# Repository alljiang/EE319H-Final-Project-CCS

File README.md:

# EE319H-Final-Project-CCS
Smash Bros TM4C edition, written in Code Exploder Studio. Using custom drivers and framework.  
Submission for the final project (lab 10 game design competition) of EE319H.  

Features:  
  • 3 characters: Kirby, Game and Watch, and a newcomer: Dr. Jon Valvano  
  • 6 stages: Final Destination, Battlefield, Smashville, UT Main Mall (original), UT EER (original), UT Gregory Gym (original)  
  • 32K audio SD card streaming  
  • Master-Slave controller interface between TM4Cs   
&nbsp;&nbsp;&nbsp;&nbsp;&nbsp;&nbsp;‣ Master controller receives player inputs from both controllers and controls game logic and audio  
&nbsp;&nbsp;&nbsp;&nbsp;&nbsp;&nbsp;‣ Slave controller receives sprite data from Master controller and updates both LCD displays  
  • 1 megabyte flash memory used by slave controller for fast access to raw sprite data  
  • Custom drivers for flash memory and ILI9341 LCD display  
  • Custom PCB - schematic and 3D assembly included in files   
  • [Game Simulator](https://github.com/alljiang/EE319H-Final-Project-Simulation), which was used to develop the 8000+ lines of game logic  

Watch the demo here: https://www.youtube.com/watch?v=PevV5ol1qZk

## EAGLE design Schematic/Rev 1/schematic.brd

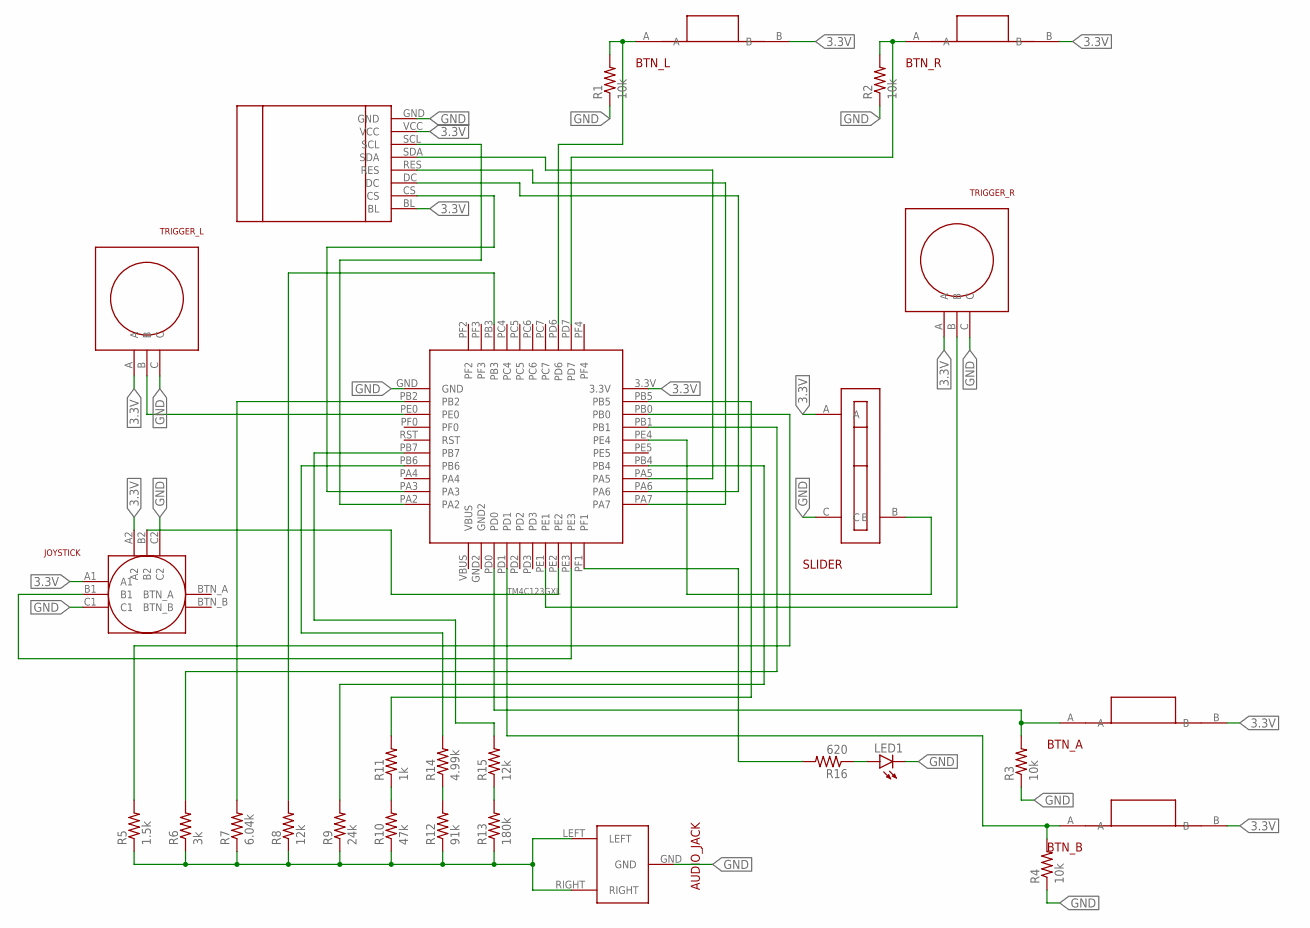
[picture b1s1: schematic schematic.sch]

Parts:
LED1: LEDCHIPLED_1206; CHIPLED_1206
R1, R2, R3, R4: 10k; R0805
R5: 1.5k; R0805
R6: 3k; R0805
R7: 6.04k; R0805
R8, R15: 12k; R0805
R9: 24k; R0805
R10: 47k; R0805
R11: 1k; R0805
R12: 91k; R0805
R13: 180k; R0805
R14: 4.99k; R0805
R16: 620; R0805
U$1: TM4C123GXL
U$2: JOYSTICK
U$3: BTN_L; RIGHT_ANGLE_BUTTON
U$4: BTN_R; RIGHT_ANGLE_BUTTON
U$5: TRIGGER_L
U$6: TRIGGER_R
U$7: SLIDER
U$8: BTN_A; BUTTON
U$9: BTN_B; BUTTON
U$10: AUDIO_JACK
U$11: LCD_SCREEN

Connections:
3.3V: U$1.3.3V, U$2.A1, U$2.A2, U$3.B, U$4.B, U$5.A, U$6.A, U$7.A, U$8.B, U$9.B, U$11.BL, U$11.VCC
GND: LED1.C, R1.1, R2.1, R3.1, R4.1, U$1.GND, U$2.C1, U$2.C2, U$5.C, U$6.C, U$7.C, U$10.GND, U$11.GND
unnamed: U$1.PE4, U$7.B
unnamed: U$1.PE0, U$5.B
unnamed: U$1.PE1, U$6.B
unnamed: U$1.PE2, U$2.B2
unnamed: R16.2, U$1.PF1
unnamed: R4.2, U$1.PD1, U$9.A
unnamed: R10.2, R11.1
unnamed: R2.2, U$1.PD7, U$4.A
unnamed: R1.2, U$1.PD6, U$3.A
unnamed: R12.2, R14.1
unnamed: U$1.PA2, U$11.SCL
unnamed: U$1.PA5, U$11.SDA
unnamed: U$1.PA7, U$11.RES
unnamed: U$1.PA6, U$11.DC
unnamed: U$1.PA3, U$11.CS
unnamed: R13.2, R15.1
unnamed: R5.1, R6.1, R7.1, R8.1, R9.1, R10.1, R12.1, R13.1, U$10.LEFT, U$10.RIGHT
unnamed: R5.2, U$1.PB0
unnamed: R6.2, U$1.PB1
unnamed: R7.2, U$1.PB2
unnamed: R8.2, U$1.PB3
unnamed: R9.2, U$1.PB4
unnamed: R11.2, U$1.PB5
unnamed: R14.2, U$1.PB6
unnamed: R15.2, U$1.PB7
unnamed: R3.2, U$1.PD0, U$8.A
unnamed: LED1.A, R16.1
unnamed: U$1.PE3, U$2.B1

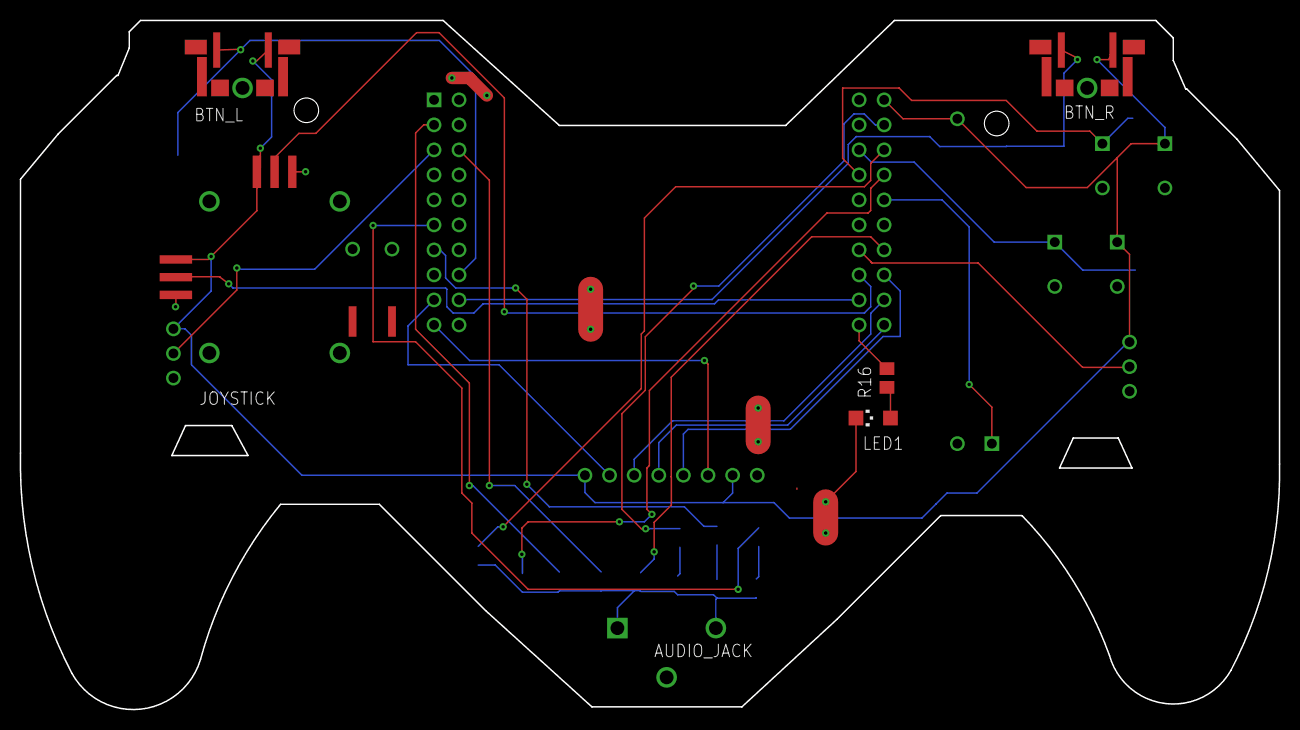
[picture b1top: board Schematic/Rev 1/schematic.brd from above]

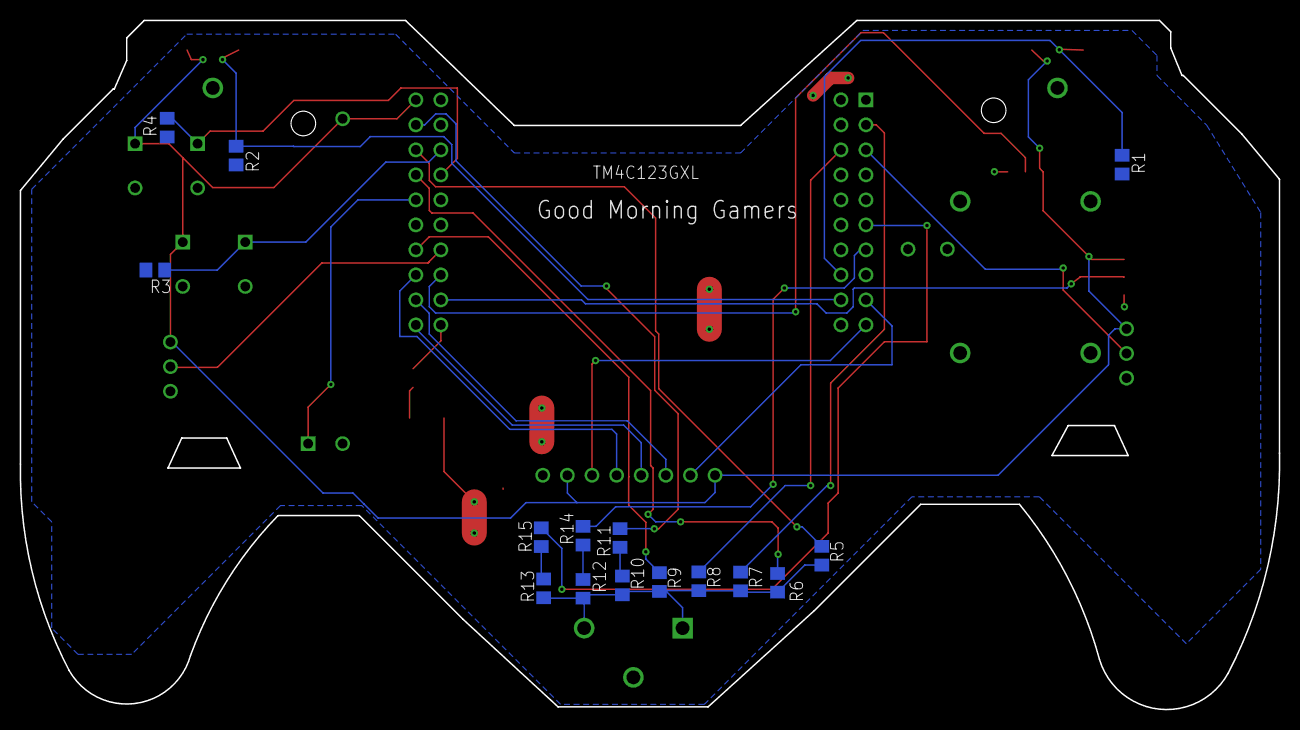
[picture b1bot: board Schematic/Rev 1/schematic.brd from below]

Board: 2 copper layers, 127.9 x 70.0 mm, 28 parts (17 on the bottom side), 30 nets.

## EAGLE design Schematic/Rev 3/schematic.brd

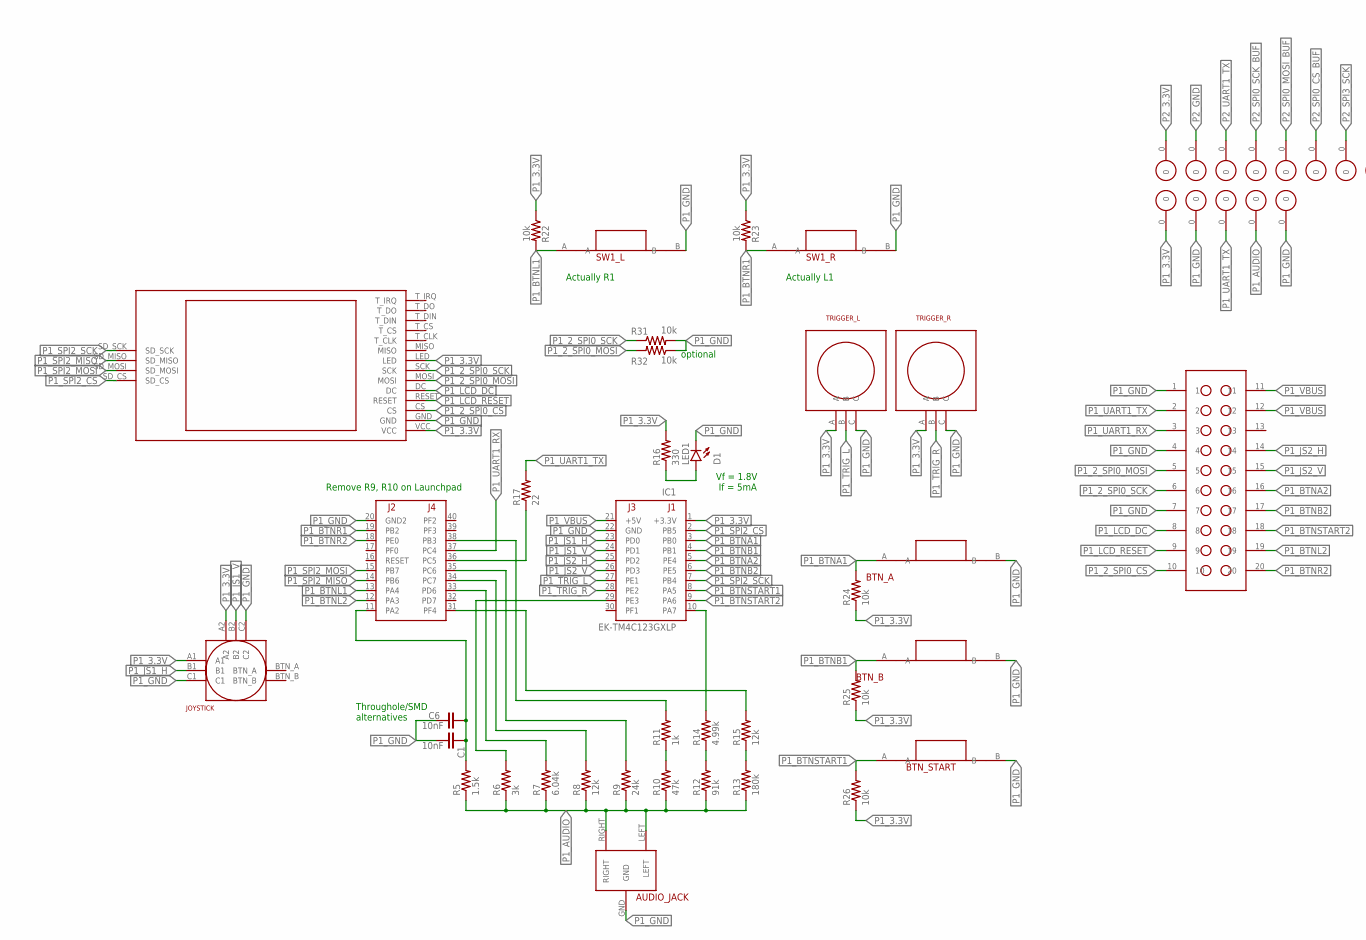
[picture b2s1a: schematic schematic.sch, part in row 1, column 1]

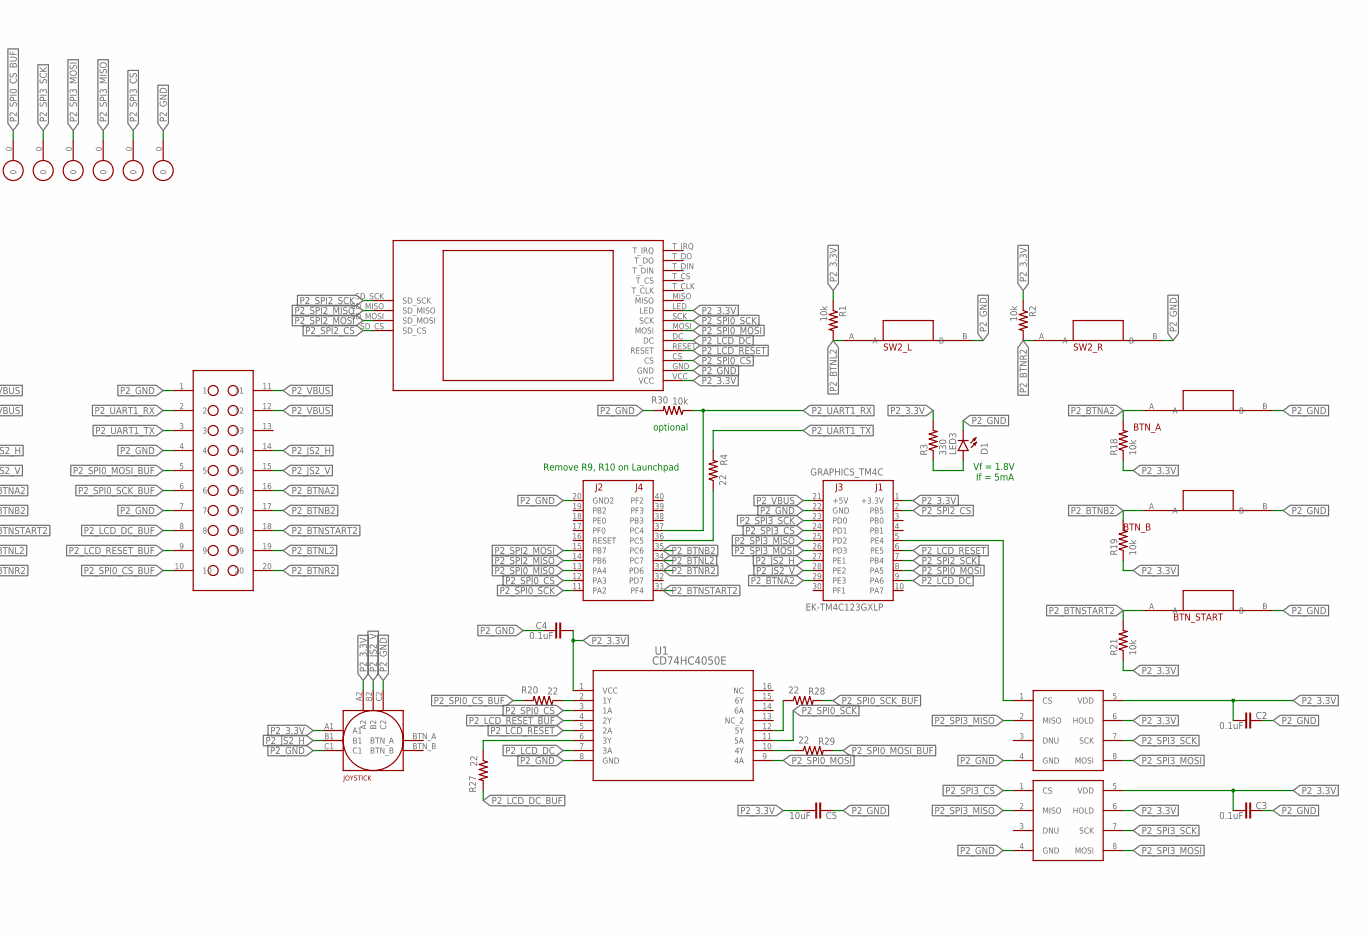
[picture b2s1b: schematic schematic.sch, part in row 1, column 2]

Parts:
C1: 10nF; C050-024X044
C2, C3, C4: 0.1uF; C0805
C5: 10uF; C0805
C6: 10nF; C0805
GRAPHICS_TM4C: EK-TM4C123GXLP; TM4C123LAUNCHPAD
IC1: EK-TM4C123GXLP; TM4C123LAUNCHPAD
LED1, LED3: D1; CHIPLED_1206
P1_3.3V: 3.3v; TESTPOINT
P1_AUDIO, P1_GND, P1_GND1, P1_UART, P2_3.3V, P2_GND, P2_GND1, P2_SPI0_CS_BUF, P2_SPI0_MOSI_BUF, P2_SPI0_SCK_BUF, P2_SPI3_CS, P2_SPI3_MISO, P2_SPI3_MOSI, P2_SPI3_SCK_BUF, P2_UART1_TX: TESTPOINT
P1_LCD, P2_LCD: ILI9341
R1, R2, R18, R19, R21, R22, R23, R24, R25, R26, R30, R31, R32: 10k; R0805
R3, R16: 330; R0805
R4, R17, R20, R27, R28, R29: 22; R0805
R5: 1.5k; R0805
R6: 3k; R0805
R7: 6.04k; R0805
R8, R15: 12k; R0805
R9: 24k; R0805
R10: 47k; R0805
R11: 1k; R0805
R12: 91k; R0805
R13: 180k; R0805
R14: 4.99k; R0805
U1: CD74HC4050E; N16
U$2, U$13: JOYSTICK
U$3: SW2_R; SW-1825968-2
U$4: SW2_L; SW-1825968-2
U$5: TRIGGER_L
U$6: TRIGGER_R
U$7, U$8: IS62WVS5128FALL-16NLI; SOIC127P600X144-8
U$10: AUDIO_JACK
U$11, U$12: 10X2_HEADER
U$14, U$20: BTN_A; BUTTON
U$15, U$23: BTN_B; BUTTON
U$17, U$24: BTN_START; BUTTON
U$18: SW1_R; SW-1825968-2
U$19: SW1_L; SW-1825968-2

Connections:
unnamed: IC1.29 (PE3), R6.2
unnamed: C1.1, C6.1, IC1.11 (PA2), R5.2
unnamed: GRAPHICS_TM4C.5 (PE4), U$8.1 (CS)
unnamed: LED3.A, R3.1
unnamed: IC1.31 (PF4), R15.2
unnamed: R10.2, R11.1
unnamed: R20.1, U1.2 (1Y)
unnamed: IC1.33 (PD6), R7.2
unnamed: R12.2, R14.1
unnamed: LED1.A, R16.1
unnamed: IC1.34 (PC7), R8.2
unnamed: IC1.35 (PC6), R9.2
unnamed: IC1.36 (PC5), R17.1
unnamed: R13.2, R15.1
unnamed: R27.1, U1.6 (3Y)
unnamed: IC1.38 (PB3), R11.2
unnamed: IC1.10 (PA7), R14.2
unnamed: R28.1, U1.12 (5Y)
unnamed: R29.1, U1.10 (4Y)
unnamed: GRAPHICS_TM4C.36 (PC5), R4.1
P1_2_SPI0_CS: P1_LCD.CS, U$11.10
P1_2_SPI0_MOSI: P1_LCD.MOSI, R32.2, U$11.5
P1_2_SPI0_SCK: P1_LCD.SCK, R31.1, U$11.6
P1_3.3V: IC1.1 (+3.3V), P1_3.3V.0, P1_LCD.LED, P1_LCD.VCC, R16.2, R22.1, R23.1, R24.1, R25.1, R26.1, U$2.A1, U$2.A2, U$5.A, U$6.A
P1_AUDIO: P1_AUDIO.0, R5.1, R6.1, R7.1, R8.1, R9.1, R10.1, R12.1, R13.1, U$10.LEFT, U$10.RIGHT
P1_BTNA1: IC1.3 (PB0), R24.2, U$20.A
P1_BTNA2: IC1.5 (PE4), U$11.16
P1_BTNB1: IC1.4 (PB1), R25.2, U$23.A
P1_BTNB2: IC1.6 (PE5), U$11.17
P1_BTNL1: IC1.13 (PA4), R22.2, U$19.A
P1_BTNL2: IC1.12 (PA3), U$11.19
P1_BTNR1: IC1.19 (PB2), R23.2, U$18.A
P1_BTNR2: IC1.18 (PE0), U$11.20
P1_BTNSTART1: IC1.8 (PA5), R26.2, U$24.A
P1_BTNSTART2: IC1.9 (PA6), U$11.18
P1_GND: C1.2, C6.2, IC1.20 (GND2), IC1.22 (GND), LED1.C, P1_GND.0, P1_GND1.0, P1_LCD.GND, R31.2, R32.1, U$2.C1, U$2.C2, U$5.C, U$6.C, U$10.GND, U$11.1, U$11.4, U$11.7, U$18.B, U$19.B, U$20.B, U$23.B, U$24.B
P1_JS1_H: IC1.23 (PD0), U$2.B1
P1_JS1_V: IC1.24 (PD1), U$2.B2
P1_JS2_H: IC1.25 (PD2), U$11.14
P1_JS2_V: IC1.26 (PD3), U$11.15
P1_LCD_DC: P1_LCD.DC, U$11.8
P1_LCD_RESET: P1_LCD.RESET, U$11.9
P1_SPI2_CS: IC1.2 (PB5), P1_LCD.SD_CS
P1_SPI2_MISO: IC1.14 (PB6), P1_LCD.SD_MISO
P1_SPI2_MOSI: IC1.15 (PB7), P1_LCD.SD_MOSI
P1_SPI2_SCK: IC1.7 (PB4), P1_LCD.SD_SCK
P1_TRIG_L: IC1.27 (PE1), U$5.B
P1_TRIG_R: IC1.28 (PE2), U$6.B
P1_UART1_RX: IC1.37 (PC4), U$11.3
P1_UART1_TX: P1_UART.0, R17.2, U$11.2
P1_VBUS: IC1.21 (+5V), U$11.11, U$11.12
P2_3.3V: C2.2, C3.2, C4.1, C5.2, GRAPHICS_TM4C.1 (+3.3V), P2_3.3V.0, P2_LCD.LED, P2_LCD.VCC, R1.1, R2.1, R3.2, R18.1, R19.1, R21.1, U1.1 (VCC), U$7.5 (VDD), U$7.6 (HOLD), U$8.5 (VDD), U$8.6 (HOLD), U$13.A1, U$13.A2
P2_BTNA2: GRAPHICS_TM4C.29 (PE3), R18.2, U$12.16, U$14.A
P2_BTNB2: GRAPHICS_TM4C.35 (PC6), R19.2, U$12.17, U$15.A
P2_BTNL2: GRAPHICS_TM4C.34 (PC7), R1.2, U$4.A, U$12.19
P2_BTNR2: GRAPHICS_TM4C.33 (PD6), R2.2, U$3.A, U$12.20
P2_BTNSTART2: GRAPHICS_TM4C.31 (PF4), R21.2, U$12.18, U$17.A
P2_GND: C2.1, C3.1, C4.2, C5.1, GRAPHICS_TM4C.20 (GND2), GRAPHICS_TM4C.22 (GND), LED3.C, P2_GND.0, P2_GND1.0, P2_LCD.GND, R30.2, U1.8 (GND), U$3.B, U$4.B, U$7.4 (GND), U$8.4 (GND), U$12.1, U$12.4, U$12.7, U$13.C1, U$13.C2, U$14.B, U$15.B, U$17.B
P2_JS2_H: GRAPHICS_TM4C.27 (PE1), U$12.14, U$13.B1
P2_JS2_V: GRAPHICS_TM4C.28 (PE2), U$12.15, U$13.B2
P2_LCD_DC: GRAPHICS_TM4C.9 (PA6), P2_LCD.DC, U1.7 (3A)
P2_LCD_DC_BUF: R27.2, U$12.8
P2_LCD_RESET: GRAPHICS_TM4C.6 (PE5), P2_LCD.RESET, U1.5 (2A)
P2_LCD_RESET_BUF: U1.4 (2Y), U$12.9
P2_SPI0_CS: GRAPHICS_TM4C.12 (PA3), P2_LCD.CS, U1.3 (1A)
P2_SPI0_CS_BUF: P2_SPI0_CS_BUF.0, R20.2, U$12.10
P2_SPI0_MISO: GRAPHICS_TM4C.13 (PA4)
P2_SPI0_MOSI: GRAPHICS_TM4C.8 (PA5), P2_LCD.MOSI, U1.9 (4A)
P2_SPI0_MOSI_BUF: P2_SPI0_MOSI_BUF.0, R29.2, U$12.5
P2_SPI0_SCK: GRAPHICS_TM4C.11 (PA2), P2_LCD.SCK, U1.11 (5A)
P2_SPI0_SCK_BUF: P2_SPI0_SCK_BUF.0, R28.2, U$12.6
P2_SPI2_CS: GRAPHICS_TM4C.2 (PB5), P2_LCD.SD_CS
P2_SPI2_MISO: GRAPHICS_TM4C.14 (PB6), P2_LCD.SD_MISO
P2_SPI2_MOSI: GRAPHICS_TM4C.15 (PB7), P2_LCD.SD_MOSI
P2_SPI2_SCK: GRAPHICS_TM4C.7 (PB4), P2_LCD.SD_SCK
P2_SPI3_CS: GRAPHICS_TM4C.24 (PD1), P2_SPI3_CS.0, U$7.1 (CS)
P2_SPI3_MISO: GRAPHICS_TM4C.25 (PD2), P2_SPI3_MISO.0, U$7.2 (MISO), U$8.2 (MISO)
P2_SPI3_MOSI: GRAPHICS_TM4C.26 (PD3), P2_SPI3_MOSI.0, U$7.8 (MOSI), U$8.8 (MOSI)
P2_SPI3_SCK: GRAPHICS_TM4C.23 (PD0), P2_SPI3_SCK_BUF.0, U$7.7 (SCK), U$8.7 (SCK)
P2_UART1_RX: GRAPHICS_TM4C.37 (PC4), R30.1, U$12.2
P2_UART1_TX: P2_UART1_TX.0, R4.2, U$12.3
P2_VBUS: GRAPHICS_TM4C.21 (+5V), U$12.11, U$12.12

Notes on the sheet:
Remove R9, R10 on Launchpad
Vf = 1.8V If = 5mA
optional
Throughole/SMD alternatives
Actually R1
Actually L1

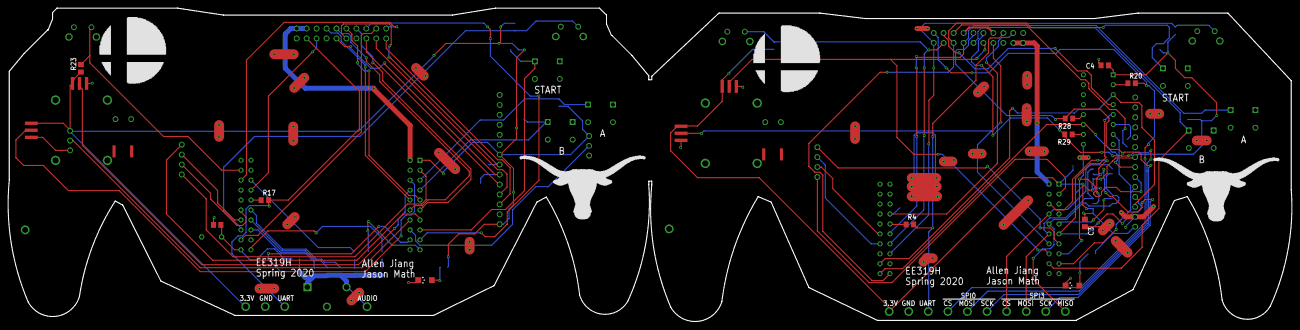
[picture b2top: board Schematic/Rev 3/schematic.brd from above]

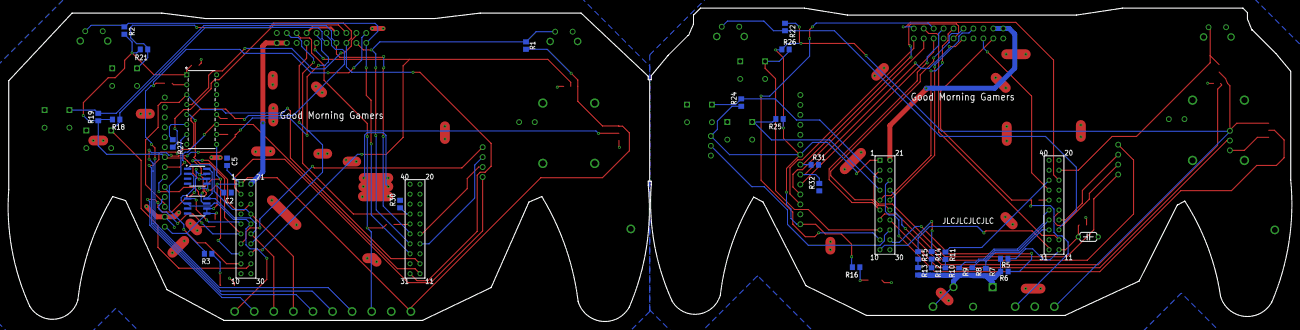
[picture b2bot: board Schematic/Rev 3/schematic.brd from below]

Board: 2 copper layers, 327.9 x 80.0 mm, 80 parts (36 on the bottom side), 81 nets.

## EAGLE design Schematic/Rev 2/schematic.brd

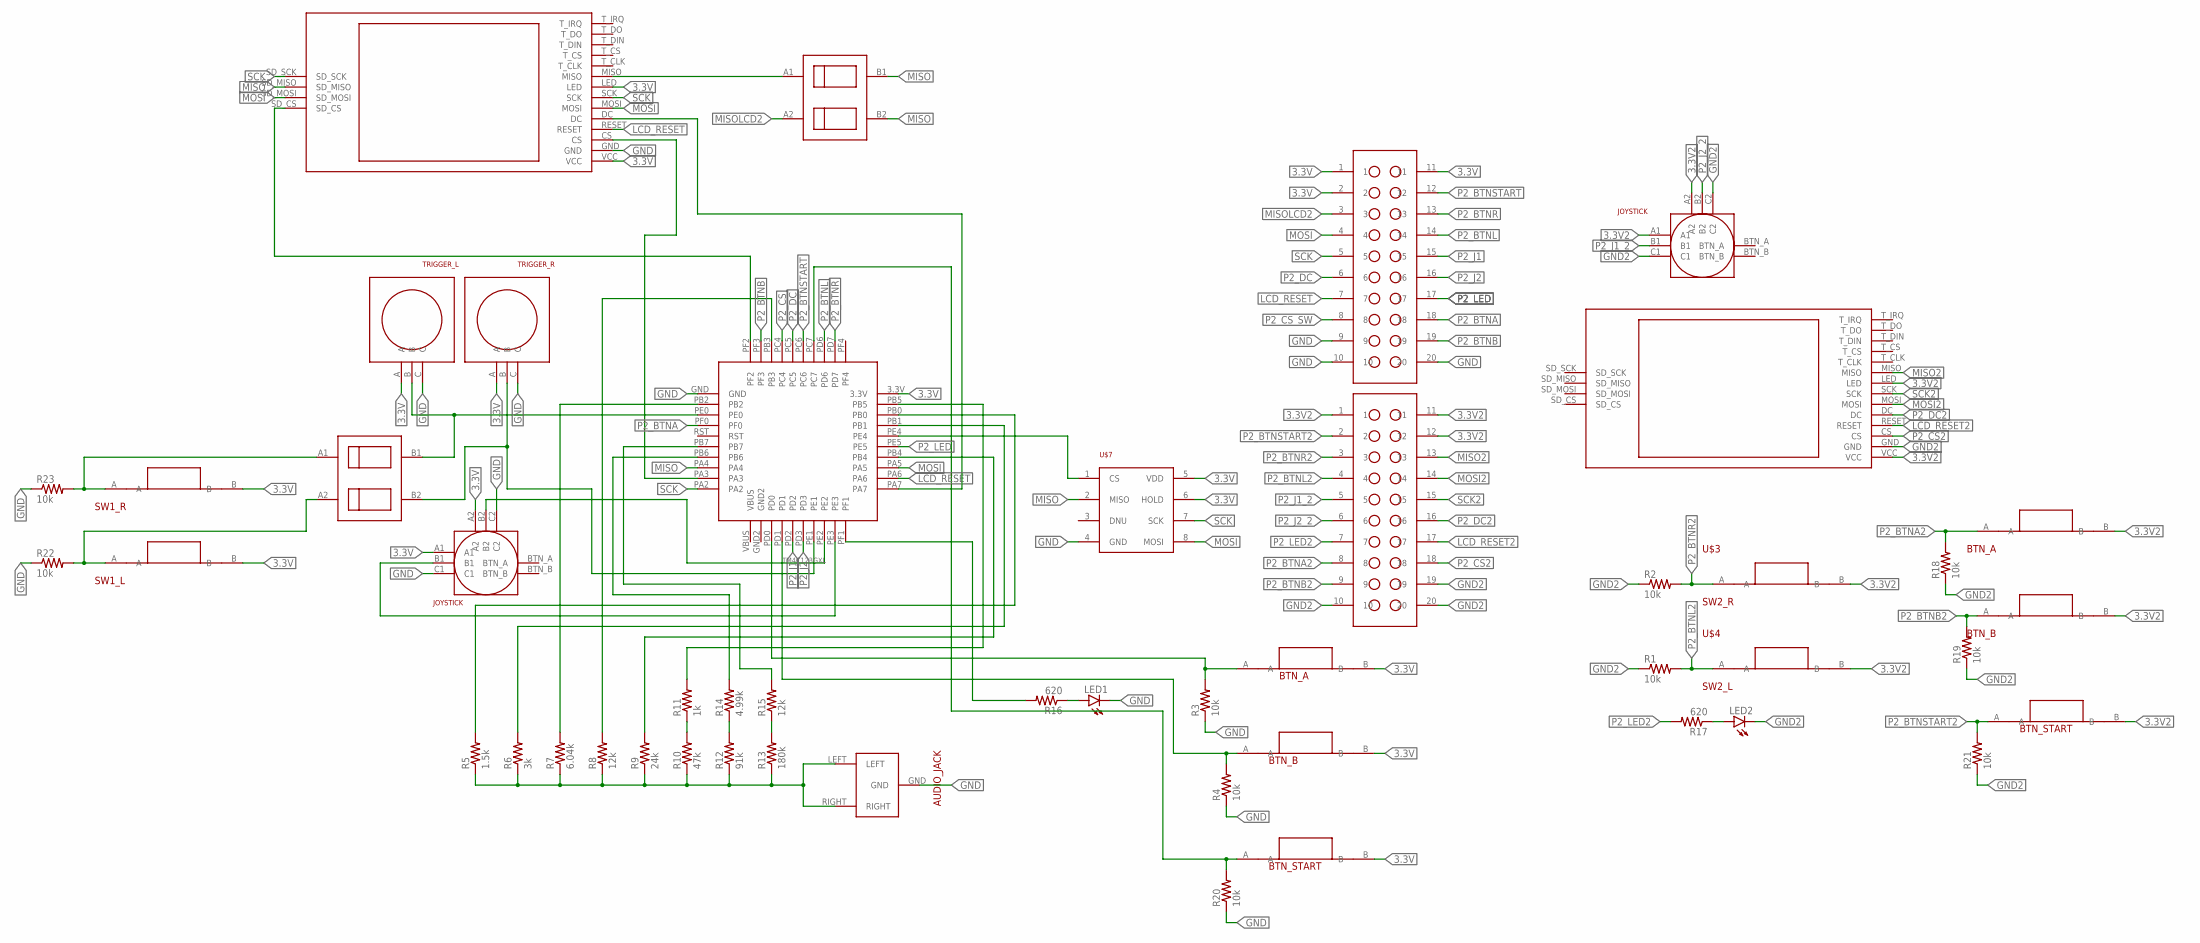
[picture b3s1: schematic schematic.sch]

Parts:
LED1, LED2: LEDCHIPLED_1206; CHIPLED_1206
P1_LCD, P2_LCD: ILI9341
R1, R2, R3, R4, R18, R19, R20, R21, R22, R23: 10k; R0805
R5: 1.5k; R0805
R6: 3k; R0805
R7: 6.04k; R0805
R8, R15: 12k; R0805
R9: 24k; R0805
R10: 47k; R0805
R11: 1k; R0805
R12: 91k; R0805
R13: 180k; R0805
R14: 4.99k; R0805
R16, R17: 620; R0805
U$1: TM4C123GXL
U$2, U$13: JOYSTICK
U$3: SW2_R; SW-1825968-2
U$4: SW2_L; SW-1825968-2
U$5: TRIGGER_L
U$6: TRIGGER_R
U$7: IS62WVS5128FALL-16NLI; SOIC127P600X144-8
U$8, U$14: BTN_A; BUTTON
U$9, U$15: BTN_B; BUTTON
U$10: AUDIO_JACK
U$11, U$12: 10X2_HEADER
U$16, U$17: BTN_START; BUTTON
U$18: SW1_R; SW-1825968-2
U$19: SW1_L; SW-1825968-2
U$20, U$21: DIPSW-2

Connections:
3.3V: P1_LCD.LED, P1_LCD.VCC, U$1.3.3V, U$2.A1, U$2.A2, U$5.A, U$6.A, U$7.5 (VDD), U$7.6 (HOLD), U$8.B, U$9.B, U$11.1, U$11.2, U$11.11, U$16.B, U$18.B, U$19.B
3.3V2: P2_LCD.LED, P2_LCD.VCC, U$3.B, U$4.B, U$12.1, U$12.11, U$12.12, U$13.A1, U$13.A2, U$14.B, U$15.B, U$17.B
GND: LED1.C, P1_LCD.GND, R3.1, R4.1, R20.1, R22.1, R23.1, U$1.GND, U$2.C1, U$2.C2, U$5.C, U$6.C, U$7.4 (GND), U$10.GND, U$11.9, U$11.10, U$11.20
GND2: LED2.C, P2_LCD.GND, R1.1, R2.1, R18.1, R19.1, R21.1, U$12.10, U$12.19, U$12.20, U$13.C1, U$13.C2
LCD_RESET: P1_LCD.RESET, U$1.PA6, U$11.7
LCD_RESET2: P2_LCD.RESET, U$12.17
MISO: P1_LCD.SD_MISO, U$1.PA4, U$7.2 (MISO), U$21.B1, U$21.B2
MISO2: P2_LCD.MISO, U$12.13
MISOLCD1: P1_LCD.MISO, U$21.A1
MISOLCD2: U$11.3, U$21.A2
MOSI: P1_LCD.MOSI, P1_LCD.SD_MOSI, U$1.PA5, U$7.8 (MOSI), U$11.4
MOSI2: P2_LCD.MOSI, U$12.14
unnamed: U$1.PE4, U$7.1 (CS)
unnamed: U$1.PE0, U$5.B, U$20.B1
unnamed: P1_LCD.CS, U$1.PA3
unnamed: U$1.PE2, U$2.B2
unnamed: U$1.PE1, U$6.B, U$20.B2
unnamed: R16.2, U$1.PF1
unnamed: R4.2, U$1.PD1, U$9.A
unnamed: R10.2, R11.1
unnamed: LED2.A, R17.1
unnamed: R12.2, R14.1
unnamed: R20.2, U$1.PC7, U$16.A
unnamed: P1_LCD.DC, U$1.PA7
unnamed: R13.2, R15.1
unnamed: R5.1, R6.1, R7.1, R8.1, R9.1, R10.1, R12.1, R13.1, U$10.LEFT, U$10.RIGHT
unnamed: R5.2, U$1.PB0
unnamed: R6.2, U$1.PB1
unnamed: R7.2, U$1.PB2
unnamed: R8.2, U$1.PB3
unnamed: R9.2, U$1.PB4
unnamed: R11.2, U$1.PB5
unnamed: R14.2, U$1.PB6
unnamed: R15.2, U$1.PB7
unnamed: R3.2, U$1.PD0, U$8.A
unnamed: LED1.A, R16.1
unnamed: U$1.PE3, U$2.B1
unnamed: P1_LCD.SD_CS, U$1.PF2
P1_BTN_L: R22.2, U$19.A, U$20.A2
P1_BTN_R: R23.2, U$18.A, U$20.A1
P2_BTNA: U$1.PF0, U$11.18
P2_BTNA2: R18.2, U$12.8, U$14.A
P2_BTNB: U$1.PF3, U$11.19
P2_BTNB2: R19.2, U$12.9, U$15.A
P2_BTNL: U$1.PD6, U$11.14
P2_BTNL2: R1.2, U$4.A, U$12.4
P2_BTNR: U$1.PD7, U$11.13
P2_BTNR2: R2.2, U$3.A, U$12.3
P2_BTNSTART: U$1.PC6, U$11.12
P2_BTNSTART2: R21.2, U$12.2, U$17.A
P2_CS: U$1.PC4
P2_CS2: P2_LCD.CS, U$12.18
P2_CS_SW: U$11.8
P2_DC: U$1.PC5, U$11.6
P2_DC2: P2_LCD.DC, U$12.16
P2_J1: U$1.PD2, U$11.15
P2_J1_2: U$12.5, U$13.B1
P2_J2: U$1.PD3, U$11.16
P2_J2_2: U$12.6, U$13.B2
P2_LED: U$1.PE5, U$11.17
P2_LED2: R17.2, U$12.7
SCK: P1_LCD.SCK, P1_LCD.SD_SCK, U$1.PA2, U$7.7 (SCK), U$11.5
SCK2: P2_LCD.SCK, U$12.15

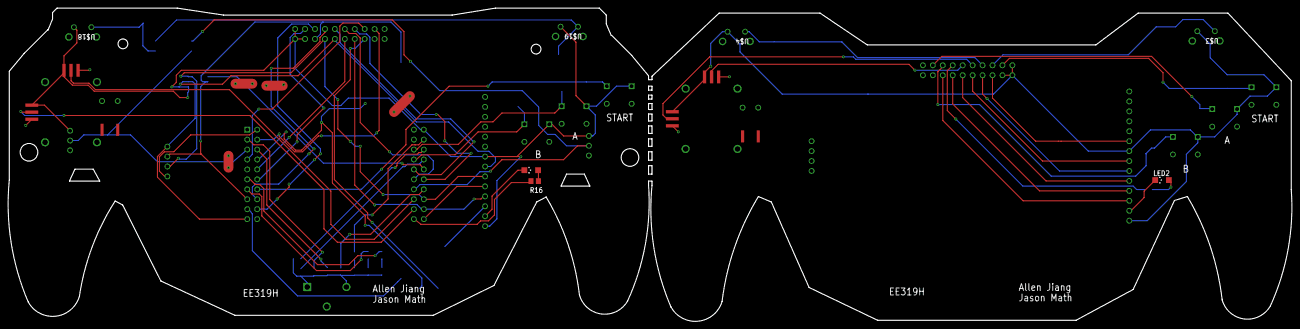
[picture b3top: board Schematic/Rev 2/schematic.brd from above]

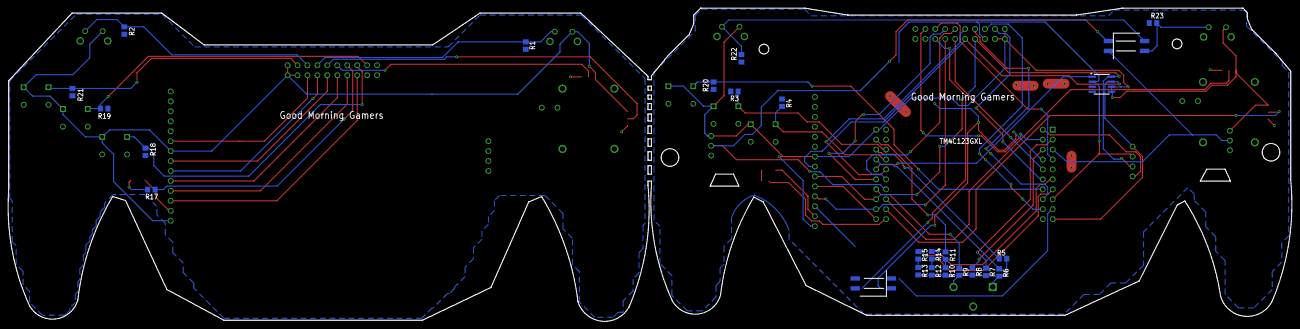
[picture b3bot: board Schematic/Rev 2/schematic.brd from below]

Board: 2 copper layers, 328.0 x 80.0 mm, 48 parts (27 on the bottom side), 61 nets.

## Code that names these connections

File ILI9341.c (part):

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 *      ST7735
 *   LED-: GND
 *   LED+: 3.3V
 *  SD_CS: PF2, SD CS
 *   MOSI: PA5, SD MOSI
 *   MISO: PA4, SD MISO
 *    SCK: PA2, SD clock
 *     CS: PA3
 *    SCL: PA2
 *    SDA: PA5
 *     A0: PA7
 *  RESET: PA6
 *     NC: not connected
 *     NC: not connected
 *     NC: not connected
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    SYSCTL_RCGCGPIO_R |= 0x01; // activate port A
    while((SYSCTL_PRGPIO_R&0x01)==0){}; // allow time for clock to start

    GPIO_PORTA_DIR_R |= 0x8;             // make PA3 out
    GPIO_PORTA_AFSEL_R &= ~0x8;          // disable alt funct on PA3
    GPIO_PORTA_DEN_R |= 0x8;             // enable digital I/O on PA3

    //  Reset using RST pin
    chipSelect(true);
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    delay(250);   // wait 5 ms before sending commands, 120 for slpout

    // initialize SSI0
    GPIO_PORTA_AFSEL_R |= 0x2C;           // enable alt funct on PA2,3,5
    GPIO_PORTA_DEN_R |= 0x2C;             // enable digital I/O on PA2,3,5

    // configure PA2,3,5 as SSI
    GPIO_PORTA_PCTL_R = (GPIO_PORTA_PCTL_R&0xFF0F00FF)+0x00202200;
    GPIO_PORTA_AMSEL_R &= ~0x2C;          // disable analog functionality on PA2,3,5
    SSI0_CR1_R &= ~SSI_CR1_SSE;           // disable SSI
    SSI0_CR1_R &= ~SSI_CR1_MS;            // master mode

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    endSPITransaction();
}

// PA7  - D/C of LCD
// sets D/C pin     false: data (high)     true: command (low)
void setCommandPin(bool isCommand) {
    if(isCommand) {
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    }
}

//  PA6 - RST pin of board 1 & 2
//  false: no reset (low)   true: reset (high)
void setResetPin(bool reset) {
    if(reset) {
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    }
}

// PA3  - CS of board 1
// PC4  - CS of board 2
// Sets CS pin of both LCDs
void chipSelect(bool select) {
    while((SSI0_SR_R&SSI_SR_BSY)==SSI_SR_BSY){};
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
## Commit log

2020-01-29 adding sd card
2020-01-29 SD card ready for testing
2020-01-30 Added some commands
2020-02-02 Screen works! Added functions
2020-02-02 optimizations and bug fixes
2020-02-03 organizaiton
2020-02-03 stole valvano's code
2020-02-03 SO FAST
2020-02-03 add tests. YEAHHBOIIII
2020-02-03 compatibility with ILI9341
2020-02-03 adjust headers
2020-02-03 tests for ili9341
2020-02-04 ILI9341 is functional!
2020-02-04 optimizing multicolor line drawing
2020-02-05 rename Data to data
2020-02-05 organization
2020-02-05 about to rewrite SPI to use DMA library
2020-02-06 DMA library BAD
2020-02-06 Revert "DMA library BAD"
    This reverts commit 879dd2080eba2e5a9ad73d9e57da6e6b729c7685.
2020-02-06 removed all traces of attempting to dma this stuff
2020-02-07 reorganization
2020-02-07 Added SRAM driver
2020-02-16 added microsecond timing
2020-02-17 using periodic timer interrupts for sound
2020-02-17 working on audio manager
2020-02-17 changed FIFO impelementation
2020-02-18 disgusting
2020-02-18 Revert "disgusting"
    This reverts commit f41bfa5bff5f846f2f6373465d8b4c71f205cca1.
2020-02-18 i hate SD Cards
2020-02-18 i hate eveything
2020-02-18 Revert "i hate eveything"
    This reverts commit ddd88baec2011a713ebd9f8c0af749a1e5d65279.
2020-02-18 Revert "Revert "i hate eveything""
    This reverts commit 99fb3881315889f29b93a83d7142bf9253112ee7.
2020-02-18 WHHATTT TTHEEE HEECCKKKKKKK
2020-02-18 increased stack size
2020-02-19 it's kinda reading correctly now
2020-02-19 it's streaming!!!
2020-02-20 YEAHBOIII
2020-02-22 working on timer interrupt for audio
2020-02-22 pins don't work???
2020-02-22 Revert "pins don't work???"
    This reverts commit f51673376b843261b7b4dd885e16e0ce94b4b4ae.
2020-02-22 Revert "working on timer interrupt for audio"
    This reverts commit 40364d9725598ba564c017707e3a970dfc015def.
2020-02-22 Revert "Revert "working on timer interrupt for audio""
    This reverts commit 23dcd2164878133b0e34a64b7a55ad8bae470cf3.
2020-02-22 Revert "Revert "pins don't work???""
    This reverts commit 43b4ea0ea62ae2134bcb6e3514fe5b8ef0512720.
2020-02-22 using timer interrupts
2020-02-22 yeet
2020-02-22 trying to get multiple audio playing simultaneously
2020-02-22 working on simultaneous audio
2020-02-22 little modifications
2020-02-23 audio merging!
2020-02-23 volume scaling
2020-02-23 destroying audio
2020-02-25 less janky hacks
2020-02-25 a little better and worse
2020-02-25 YASSSSSS
2020-02-25 good audio!
2020-02-25 Revert "good audio!"
    This reverts commit 7ce347a9b43b9deacce24be4215b1d59eea5139b.
2020-02-25 Revert "YASSSSSS"
    This reverts commit ec5f4e67a1c22ef689d5ebbf0a75aca455728de1.
2020-02-25 Revert "a little better and worse"
    This reverts commit 5bb7979e1b3b549acf7e13fd09d05ce461ca6d46.
2020-02-25 Revert "less janky hacks"
    This reverts commit e07ce75cc60a40ec7872617f0c64b76cd32d857f.
2020-02-25 Revert "Revert "less janky hacks""
    This reverts commit 78772c7da93a2804bafcc7810325e0f10fc10751.
2020-02-25 Revert "Revert "a little better and worse""
    This reverts commit 3918e68e141c905bfb9cb076cf294761061de4b5.
2020-02-25 Revert "Revert "YASSSSSS""
    This reverts commit ecdefeb9d73dc8cdddd755f264b36115fcaf639a.
2020-02-25 Revert "Revert "good audio!""
    This reverts commit 9d59e53c392496cb55ef702941eee6871682b52e.
2020-02-25 playing multiple audio correctly
2020-03-02 lcd stufffs
2020-03-06 working with SRAM
2020-03-06 it's flash memory, not sram oops
2020-03-06 adjust write protocol for pages
2020-03-11 updated LCD pins
2020-03-11 change to c11
2020-03-11 update audio pins
2020-03-13 Separated Controller codes
2020-04-07 merging simulation and driver
2020-04-07 fixed SRAM driver
2020-04-08 Fixing UART
2020-04-08 code decomposer
2020-04-08 kirby moves!
2020-04-08 changed baud
2020-04-09 added frame skipper
2020-04-09 lagless! fixed row update bug in slave
2020-04-10 oof audio
2020-04-10 Revert "oof audio"
    This reverts commit 3690acc808a7593f9b9da3da405e1ee224e503b8.
2020-04-10 yayyyyyy no more popping in music!
2020-04-10 increased heap size a lot
2020-04-10 messing with screen
2020-04-15 kirby can feel pain now.
2020-04-17 what the heck
2020-04-17 Revert "what the heck"
    This reverts commit e0eb09223de5e90797ae37d8a98d5b8e19f5b20d.
2020-04-17 Revert "Revert "what the heck""
    This reverts commit dfeba6992c1a7b33196e6328390a9d74b8a14063.
2020-04-17 now u can fight
2020-04-18 added countdown sound effect
2020-04-18 making audio better
2020-04-29 starting merge
2020-04-29 yay the port works
2020-04-29 port complete
2020-05-02 add valvano
2020-05-02 modify default language
2020-05-02 untested merge
2020-05-02 added sfx metadata
2020-05-03 adding audio
2020-05-03 increased heap
2020-05-03 added kirby audio
2020-05-03 add data for new music
2020-05-03 coded in stage music
2020-05-04 more audio, added timer for controller
2020-05-04 weird buzzing noise
2020-05-04 ok i hate interrupts
2020-05-04 add death blast sound to valvano and gaw
2020-05-04 edit audio
2020-05-05 add valvano stun, uptilt
2020-05-05 add wav files for valvano
2020-05-05 Hi, I'm Jon Valvano
2020-05-05 add valvano sound metadata
2020-05-05 coded in valvano sounds, fixed audio bug
2020-05-05 pretty much finished
    ohboy.png
2020-05-05 added title screen
2020-05-05 added enjoy to downb for valvano
2020-05-05 fixed minor background audio bug
2020-05-08 Attatched Schematic + Datasheets. Final commit.
2020-05-08 Added 3D model assembly
2020-05-08 trying to add pic
2020-05-08 added render
2021-06-28 update arm compiler
2022-05-12 clean up
2022-05-13 update joystick control data
